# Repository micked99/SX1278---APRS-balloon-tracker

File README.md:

# SX1278
Aprs using Lora sx1278

Clone of this project, using a SX1278 Lora module or just the IC SX1278 as aprs tx, ALL credit goes to https://github.com/DO4AS/jufo-project-radiosonde
I have only made the pcb:s and edited the fw in a small way that fits my needs.

PCB for both LORA sx1278 module and barebone 1278 ic, make sure you get the correct module, at least 4 Lora models avalible with different pinout.

The sketch on the 328 works at 8Mhz or 16Mhz, Im using 8Mhz to save 5mA compared to 16Mhz

Fuses for 328: FD D9 FE

1278-Micro_2021-10-09.zip is the CAM files for pcb production/order

Latest PCB have the option for tcxo drive of the 1278, but the standard 32Mhz xo footprint can stil be used, gps antenna moved to the "top" + some small tweaks and fixes.

Adjust the "const float baud_adj = 0.952;" setting for 3 or 4 "strokes" in Direwolf, see info here https://forums.qrz.com/index.php?threads%2Fdirewolf-aprs-output.600522%2F&fbclid=IwAR0wUjOZmizGcujBzJqjSxanfelDZbqJ7fJmPpOwpc3_y3LSQ0mrltJrEoM   
I have the best decode rate with 0.950 - 0.964 depending on xo/tcxo used, so you need to tweek this for every board.

Also test the transmitted audio against this program - AFSK1200, if it decodes the audio it should maximize the chanses of your signal to be decoded while in flight
https://sourceforge.net/projects/qtmm/

DG4NOB version incorporates more telemetry readings like Temp from internal 328 sensor, Voltage, Vertical speed in m/s etc

TBTracker and horusbinary_tracker use the same pcb layout and is 100% compatible with the above, those fw transmitt, 4FSK, RTTY and Lora, original authors git at  https://github.com/RoelKroes  with small adjustment to fit "my" pcb layout

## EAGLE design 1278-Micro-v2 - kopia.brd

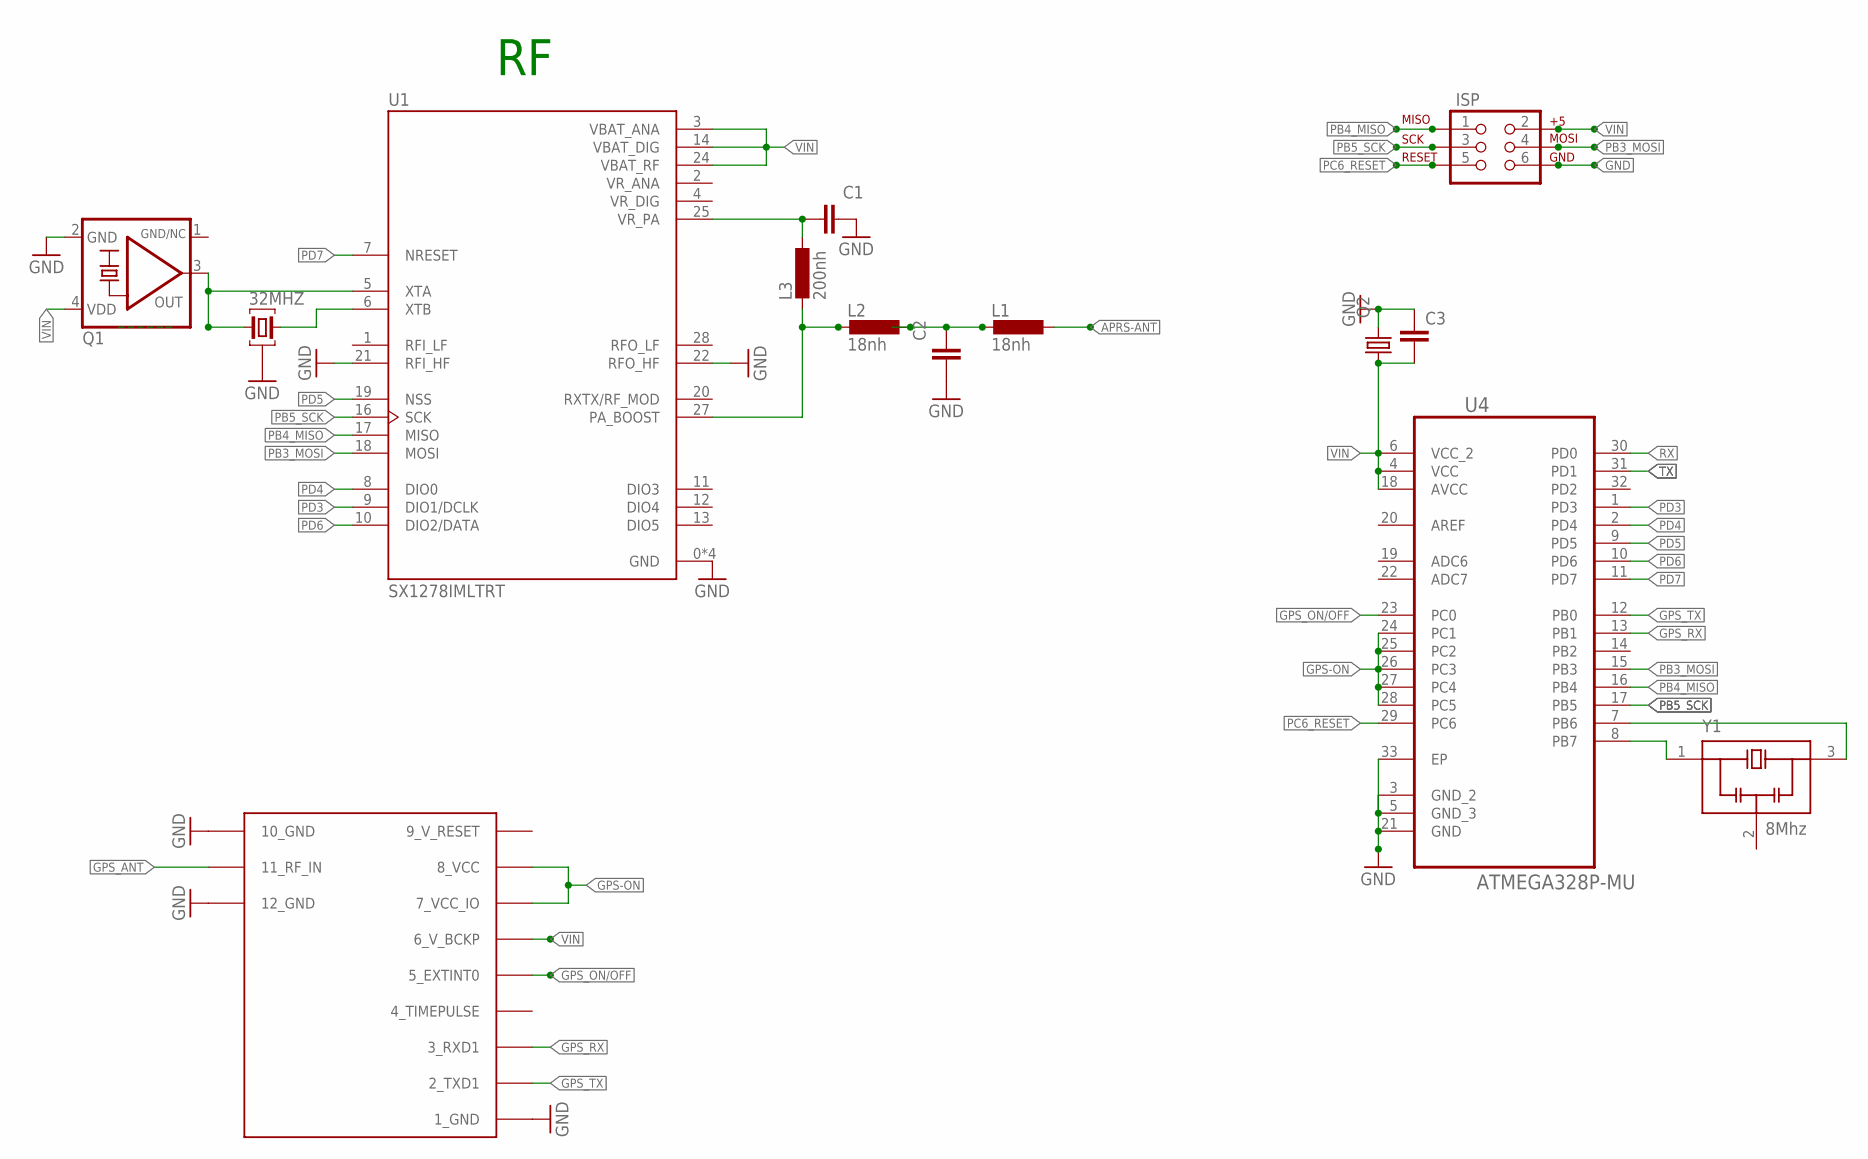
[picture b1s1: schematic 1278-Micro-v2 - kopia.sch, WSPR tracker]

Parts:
32MHZ: 16Mhz; ABM8G
C1: 100nF; C0603K
C2: 15pF; C0603K
C3: C-EUC1808; C1808
ISP: AVR_SPI_PRG_6PTH; 2X3
L1, L2: 18nh; L2012C
L3: 200nh; L2012C
Q1: TCXO 32Mhz; 3.2X2.5_KXO-84-TCXO
Q2: KX-327-NHF; 3.2X1.5
U1: SX1278IMLTRT; QFN65P600X600X100-29N
U4: ATMEGA328P-MU; QFN50P500X500X100-33N
U$2: UBLOX_MAX
Y1: 8Mhz; OSC_CSTCE12M0G15L08-R0

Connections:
9_V_RESET: U$2.9_V_RESET
AAA: 32MHZ.1, Q1.3 (OUT), U1.5 (XTA)
APRS-ANT: L1.1
GND: 32MHZ.2, 32MHZ.4 (2), C1.2, C2.1, C3.1, ISP.6, Q1.2 (GND), Q2.2, U1.0 (GND), U1.15 (GND), U1.21 (RFI_HF), U1.22 (RFO_HF), U1.23 (GND), U1.26 (GND), U4.3 (GND_2), U4.5 (GND_3), U4.21 (GND), U4.33 (EP), U$2.1_GND, U$2.10_GND, U$2.12_GND, Y1.2 (GND)
GND/NC: Q1.1 (GND/NC)
GPS-ON: U4.24 (PC1), U4.25 (PC2), U4.26 (PC3), U4.27 (PC4), U4.28 (PC5), U$2.7_VCC_IO, U$2.8_VCC
GPS_ANT: U$2.11_RF_IN
GPS_ON/OFF: U4.23 (PC0), U$2.5_EXTINT0
GPS_RX: U4.13 (PB1), U$2.3_RXD1
GPS_TX: U4.12 (PB0), U$2.2_TXD1
unnamed: U4.7 (PB6), Y1.3 (OUT)
unnamed: U4.8 (PB7), Y1.1 (IN)
unnamed: C2.2, L1.2, L2.1
unnamed: C1.1, L3.1, U1.25 (VR_PA)
unnamed: L2.2, L3.2, U1.27 (PA_BOOST)
unnamed: 32MHZ.3, U1.6 (XTB)
PB3_MOSI: ISP.4, U1.18 (MOSI), U4.15 (PB3)
PB4_MISO: ISP.1, U1.17 (MISO), U4.16 (PB4)
PB5_SCK: ISP.3, U1.16 (SCK), U4.17 (PB5)
PC6_RESET: ISP.5, U4.29 (PC6)
PD3: U1.9 (DIO1/DCLK), U4.1 (PD3)
PD4: U1.8 (DIO0), U4.2 (PD4)
PD5: U1.19 (NSS), U4.9 (PD5)
PD6: U1.10 (DIO2/DATA), U4.10 (PD6)
PD7: U1.7 (NRESET), U4.11 (PD7)
RX: U4.30 (PD0)
TX: U4.31 (PD1)
VIN: C3.2, ISP.2, Q1.4 (VDD), Q2.1, U1.3 (VBAT_ANA), U1.14 (VBAT_DIG), U1.24 (VBAT_RF), U4.4 (VCC), U4.6 (VCC_2), U4.18 (AVCC), U$2.6_V_BCKP
VR_ANA: U1.2 (VR_ANA)
VR_DIG: U1.4 (VR_DIG)

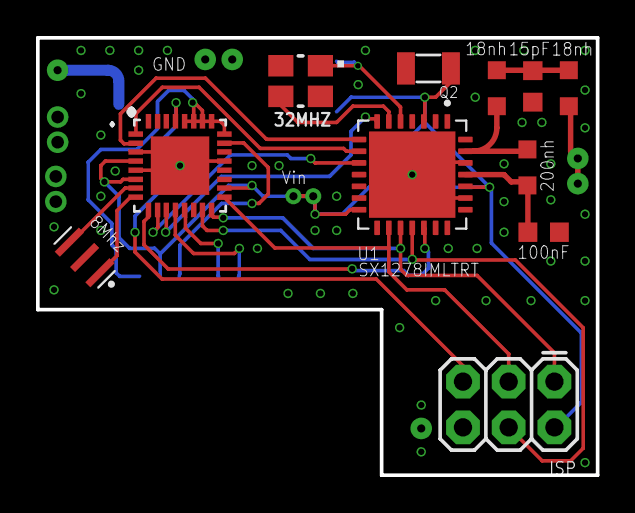
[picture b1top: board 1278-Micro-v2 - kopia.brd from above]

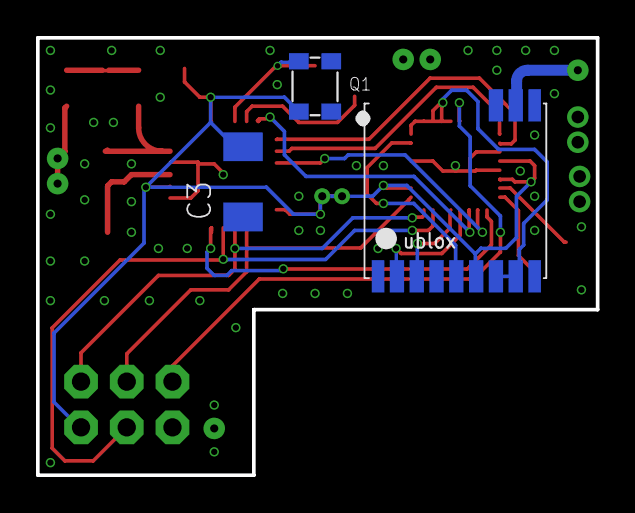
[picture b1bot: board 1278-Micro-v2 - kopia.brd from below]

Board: 2 copper layers, 31.1 x 24.3 mm, 14 parts (3 on the bottom side), 22 nets.

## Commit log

2021-12-14 Add files via upload
    The difference between original version and V2 is that this version turns off the GPS module completely and saves another 6-8mA, other then that its the same fw
2022-02-24 Rename 1278-Micro-v2 - kopia.brd to 1278-Micro-v2.brd
2025-09-26 Add files via upload
    Drop those libaries in the Arduino Library folder
2025-09-26 Libraries needed sx1278-AltSoftSerial

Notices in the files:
parts and their libraries:
crystal-geyer_V1_0: Copyright: Geyer-Electronic
